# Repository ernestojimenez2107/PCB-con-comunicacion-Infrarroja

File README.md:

<h1 align="center">📡 PCB de 4 capas · Arduino Nano + Infrarrojos</h1><p align="center">
  Del esquema eléctrico a una placa preparada para su revisión y fabricación.
  <br>
  <strong>Proyecto académico · EITE · Universidad de Las Palmas de Gran Canaria</strong>
</p>✨ ¿De qué trata el proyecto?
Diseño de una placa de circuito impreso (PCB) de cuatro capas con Arduino Nano, conectores de expansión y un sistema de transmisión y recepción por infrarrojos. El circuito integra un oscilador de aproximadamente 40 kHz basado en un temporizador SE555D, lógica digital para controlar las señales y una etapa emisora y receptora de infrarrojos.

🔁 Diagrama de bloques

```mermaid
flowchart LR
    A["Arduino Nano"] -->|TX y control| L["Lógica digital"]
    O["Oscilador SE555D · 40 kHz"] --> L
    L --> E["LED IR · TSAL4400"]
    R["Receptor IR · TSOP18440"] --> X["Lógica de recepción"]
    X -->|RX| A
```
 Componentes principales
Bloque	Componentes / función

🧠 Control	Arduino Nano y conectores de expansión

⏱️ Oscilador	SE555D, señal de ~40 kHz

📤 Emisor IR	LED TSAL4400 y transistor MMBT2222A

📥 Receptor IR	TSOP18440

🔀 Lógica digital	74LVC2G86 y 74LVC2G08

⚡ Alimentación	Redes de 5 V, 3,3 V y masa

 Diseño de la PCB

Capa	Uso principal

🔴 TOP	Pistas y conexiones de la cara superior

🟢 GND	Plano interno de masa

🟠 POWER	Distribución de alimentación

🔵 BOTTOM	Pistas y conexiones de la cara inferior

La PCB incluye conectores, taladros de fijación, serigrafía y planos de cobre.
✅ Comprobaciones realizadas
- DRC de KiCad: 0 errores y 0 avisos en la última comprobación indicada.
- Archivos de fabricación: Gerber de las cuatro capas, máscaras, serigrafías y contorno.
- Taladrado: archivos PTH y NPTH generados.
- Montaje: archivo CSV de posición de componentes generado.
- Documentación: esquemas y capas de la PCB exportados a PDF.
[!IMPORTANT]
Antes de fabricar la PCB, hay que revisar los Gerber en el visor del fabricante y confirmar la compatibilidad de las huellas, la colocación de los conectores y los modelos 3D.

📂 Organización del repositorio

Practica_Diseno_PCB/
├── Práctica_Diseño_PCB.kicad_pro    # Proyecto KiCad

├── Práctica_Diseño_PCB.kicad_sch    # Esquema principal

├── Práctica_Diseño_PCB.kicad_pcb    # Diseño de la placa

├── arduino.kicad_sch               # Arduino y expansión

├── oscilador.kicad_sch             # Oscilador de 40 kHz

├── IR_Tx_Rx.kicad_sch              # Transmisor y receptor IR

├── alimentaciones.kicad_sch       # Alimentaciones

├── Fabricacion_PCB/                # Gerber y taladrado

├── Archivos de Montaje_PCB/        # Posiciones de componentes

├── Documentacion_PDF/              # PDF del esquema y la placa

La estructura muestra los archivos principales; los nombres de las carpetas de documentación pueden variar según la entrega.

El archivo de posición de componentes se encuentra en la carpeta de montaje. La BOM y el presupuesto de 10 y 100 placas forman parte de la documentación del proyecto, cuando se incluyan en el repositorio.
🎓 Contexto académico
Proyecto desarrollado para una práctica de diseño de circuitos impresos de la Escuela de Ingeniería de Telecomunicación y Electrónica (EITE) de la Universidad de Las Palmas de Gran Canaria (ULPGC).
<p align="center"><strong>🛠️ Diseñado con KiCad </strong></p>

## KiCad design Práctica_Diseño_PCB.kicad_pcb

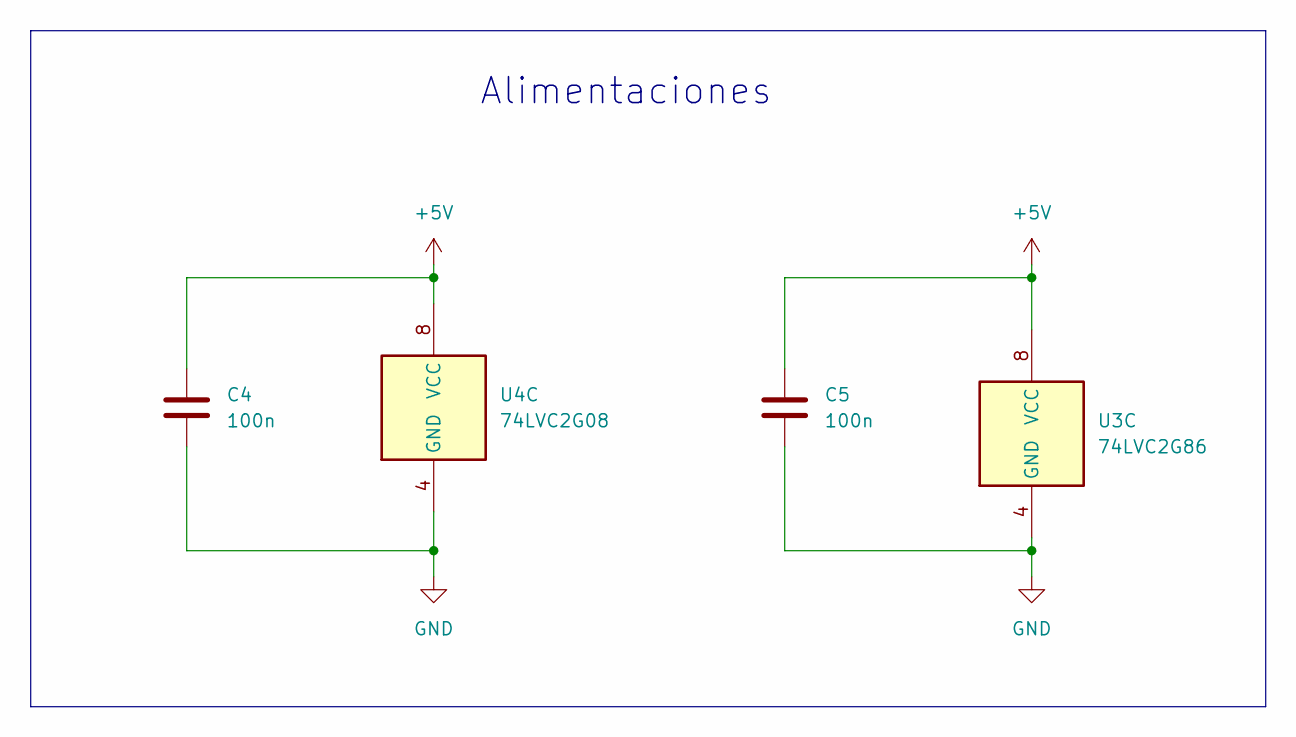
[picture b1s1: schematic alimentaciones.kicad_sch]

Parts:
C4, C5: 100n; C_0805_2012Metric_Pad1.18x1.45mm_HandSolder; DigiKey 1276-2442-1-ND
U3: 74LVC2G86; VSSOP-8_3x3mm_P0.65mm; DigiKey 296-13275-1-ND
U4: 74LVC2G08; VSSOP-8_3x3mm_P0.65mm; DigiKey 296-13263-1-ND

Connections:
+5V: C4.1, C5.1, U3.8 (VCC), U4.8 (VCC); also elsewhere on the board
GND: C4.2, C5.2, U3.4 (GND), U4.4 (GND); also elsewhere on the board

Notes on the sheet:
Alimentaciones

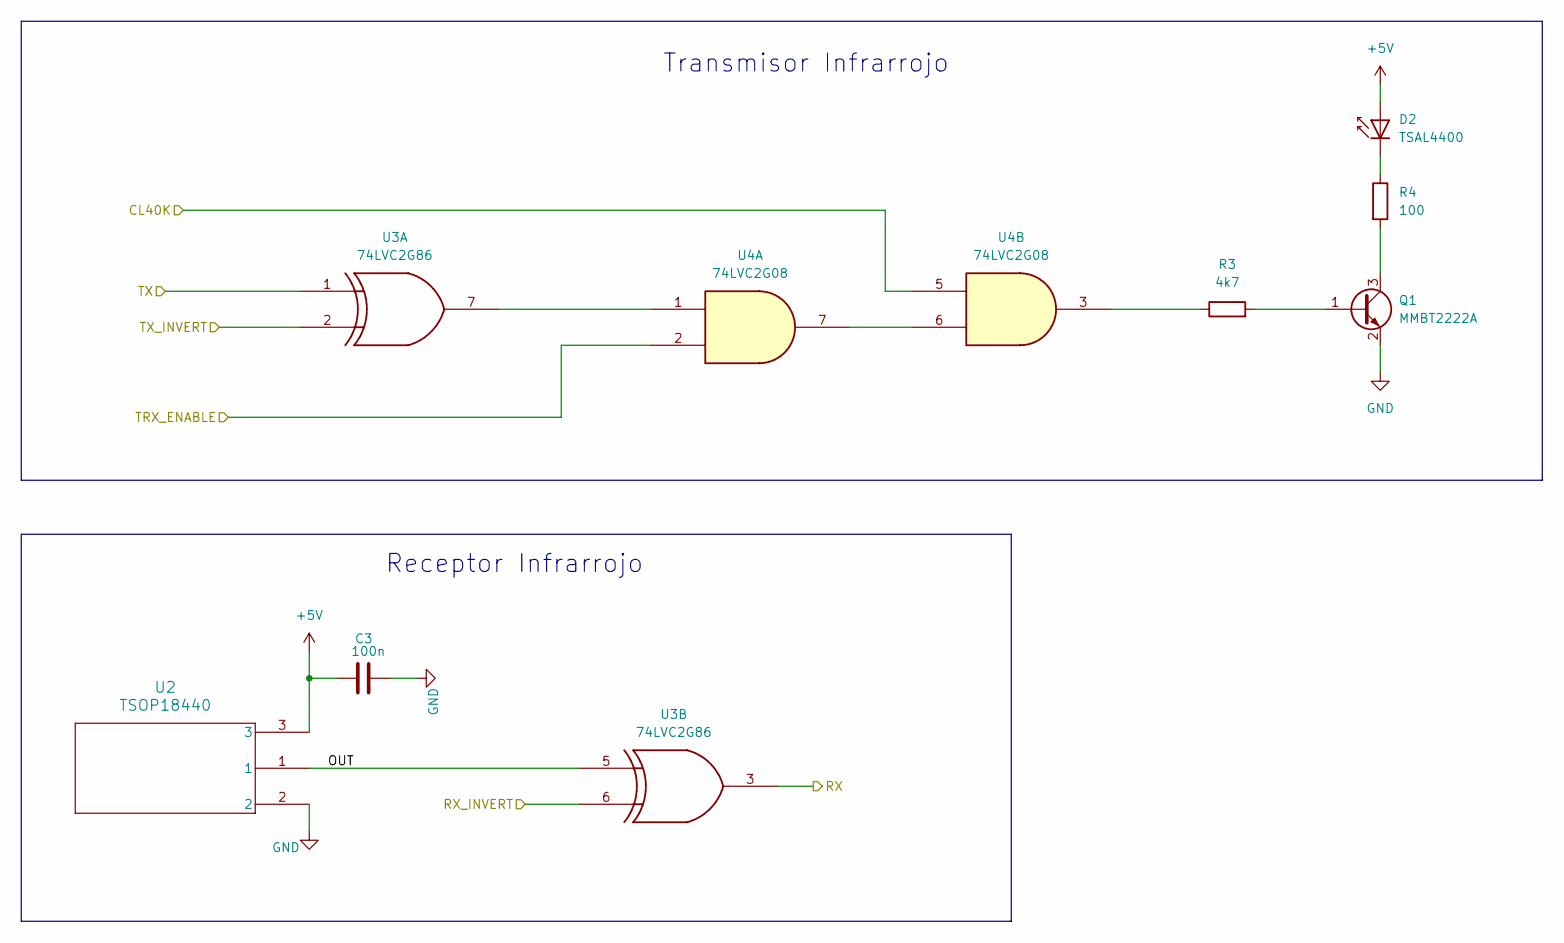
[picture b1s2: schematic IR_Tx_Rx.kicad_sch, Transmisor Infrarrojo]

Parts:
C3: 100n; C_0805_2012Metric_Pad1.18x1.45mm_HandSolder; DigiKey 1276-2442-1-ND
D2: TSAL4400; LED_D3.0mm_IRBlack; DigiKey 751-1201-ND
Q1: MMBT2222A; SOT-23; DigiKey MMBT2222ATPMSCT-ND
R3: 4k7; R_0805_2012Metric_Pad1.20x1.40mm_HandSolder; DigiKey RMCF0805JT4K70CT-ND
R4: 100; R_0805_2012Metric_Pad1.20x1.40mm_HandSolder; DigiKey RMCF0805JT100RCT-ND
U2: TSOP18440; Vishay_MOLD-3Pin; DigiKey TSOP18440-ND
U3: 74LVC2G86; VSSOP-8_3x3mm_P0.65mm; DigiKey 296-13275-1-ND
U4: 74LVC2G08; VSSOP-8_3x3mm_P0.65mm; DigiKey 296-13263-1-ND

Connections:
+5V: C3.2, D2.2 (A), U2.3; also elsewhere on the board
/Arduino Nano/RX: U3.3; also elsewhere on the board
/Arduino Nano/RX_INVERT: U3.6; also elsewhere on the board
/Arduino Nano/TRX_ENABLE: U4.2; also elsewhere on the board
/Arduino Nano/TX: U3.1; also elsewhere on the board
/Arduino Nano/TX_INVERT: U3.2; also elsewhere on the board
/Oscilador/CL40K: U4.5; also elsewhere on the board
/Tx_Rx_Infrarrojo/OUT: U2.1, U3.5
GND: C3.1, Q1.2 (E), U2.2; also elsewhere on the board
unnamed: D2.1 (K), R4.1
unnamed: Q1.1 (B), R3.2
unnamed: Q1.3 (C), R4.2
unnamed: R3.1, U4.3
unnamed: U3.7, U4.1
unnamed: U4.6, U4.7

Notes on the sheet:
Transmisor Infrarrojo
Receptor Infrarrojo

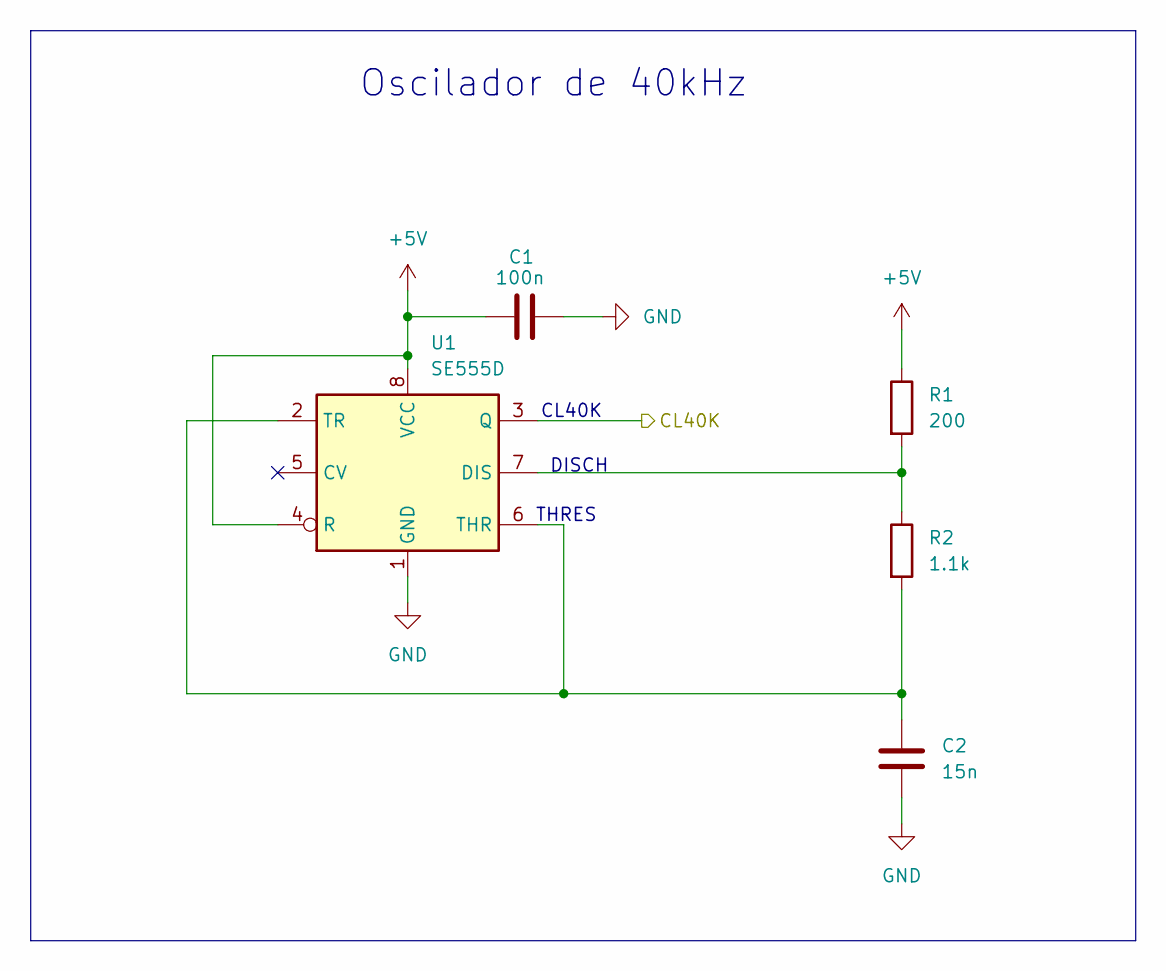
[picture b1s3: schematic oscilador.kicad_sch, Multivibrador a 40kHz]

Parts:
C1: 100n; C_0805_2012Metric_Pad1.18x1.45mm_HandSolder; DigiKey 1276-2442-1-ND
C2: 15n; C_0805_2012Metric_Pad1.18x1.45mm_HandSolder; DigiKey 311-4273-1-ND
R1: 200; R_0805_2012Metric_Pad1.20x1.40mm_HandSolder; DigiKey RMCF0805JT200RCT-ND
R2: 1.1k; R_0805_2012Metric_Pad1.20x1.40mm_HandSolder; DigiKey RMCF0805JT1K10CT-ND
U1: SE555D; SOIC-8_3.9x4.9mm_P1.27mm; DigiKey 296-6501-1-ND

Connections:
+5V: C1.1, R1.1, U1.4 (R), U1.8 (VCC); also elsewhere on the board
/Oscilador/CL40K: U1.3 (Q); also elsewhere on the board
GND: C1.2, C2.2, U1.1 (GND); also elsewhere on the board
unnamed: R1.2, R2.1, U1.7 (DIS)
unnamed: C2.1, R2.2, U1.2 (TR), U1.6 (THR)

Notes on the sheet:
THRES
DISCH
CL40K
Oscilador de 40kHz

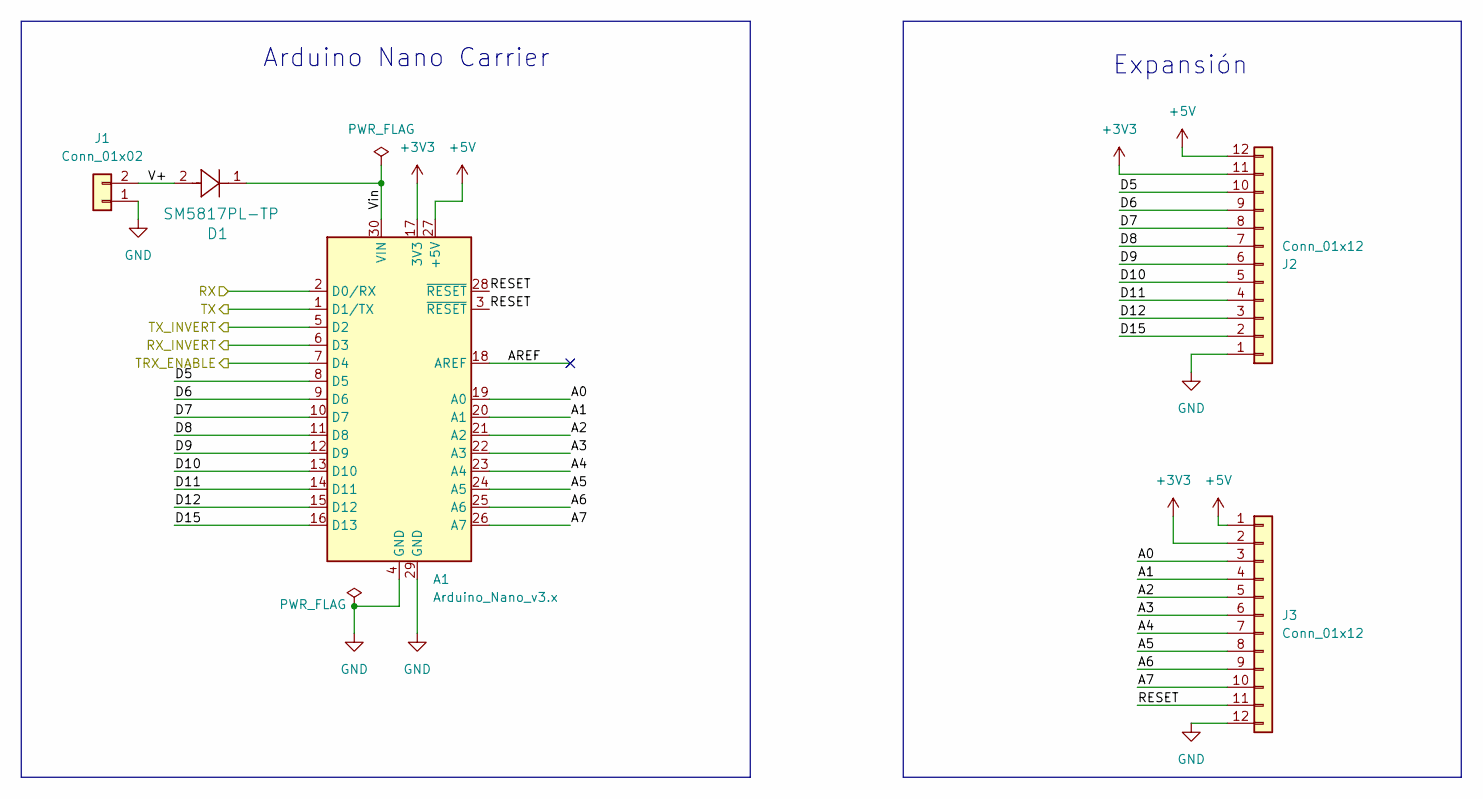
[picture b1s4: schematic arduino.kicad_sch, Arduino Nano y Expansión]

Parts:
A1: Arduino_Nano_v3.x; Arduino_Nano; DigiKey 1050-1001-ND
D1: SM5817PL-TP; CR_5817PL-TP_MCC; DigiKey SM5817PL-TPMSCT-ND
J1: Conn_01x02; 282837-2_TYC; DigiKey A113320-ND
J2, J3: Conn_01x12; PinHeader_1x12_P2.54mm_Vertical; DigiKey 2057-PH1-12-UA-ND

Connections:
+3V3: A1.17 (3V3), J2.11, J3.2
+5V: A1.27 (+5V), J2.12, J3.1; also elsewhere on the board
/Arduino Nano/A0: A1.19 (A0), J3.3
/Arduino Nano/A1: A1.20 (A1), J3.4
/Arduino Nano/A2: A1.21 (A2), J3.5
/Arduino Nano/A3: A1.22 (A3), J3.6
/Arduino Nano/A4: A1.23 (A4), J3.7
/Arduino Nano/A5: A1.24 (A5), J3.8
/Arduino Nano/A6: A1.25 (A6), J3.9
/Arduino Nano/A7: A1.26 (A7), J3.10
/Arduino Nano/AREF: A1.18 (AREF)
/Arduino Nano/D5: A1.8 (D5), J2.10
/Arduino Nano/D6: A1.9 (D6), J2.9
/Arduino Nano/D7: A1.10 (D7), J2.8
/Arduino Nano/D8: A1.11 (D8), J2.7
/Arduino Nano/D9: A1.12 (D9), J2.6
/Arduino Nano/D10: A1.13 (D10), J2.5
/Arduino Nano/D11: A1.14 (D11), J2.4
/Arduino Nano/D12: A1.15 (D12), J2.3
/Arduino Nano/D15: A1.16 (D13), J2.2
/Arduino Nano/RESET: A1.3 (~RESET), A1.28 (~RESET), J3.11
/Arduino Nano/RX: A1.2 (D0/RX); also elsewhere on the board
/Arduino Nano/RX_INVERT: A1.6 (D3); also elsewhere on the board
/Arduino Nano/TRX_ENABLE: A1.7 (D4); also elsewhere on the board
/Arduino Nano/TX: A1.1 (D1/TX); also elsewhere on the board
/Arduino Nano/TX_INVERT: A1.5 (D2); also elsewhere on the board
/Arduino Nano/V+: D1.2, J1.2
/Arduino Nano/Vin: A1.30 (VIN), D1.1
GND: A1.4 (GND), A1.29 (GND), J1.1, J2.1, J3.12; also elsewhere on the board

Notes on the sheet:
Arduino Nano Carrier
Expansión

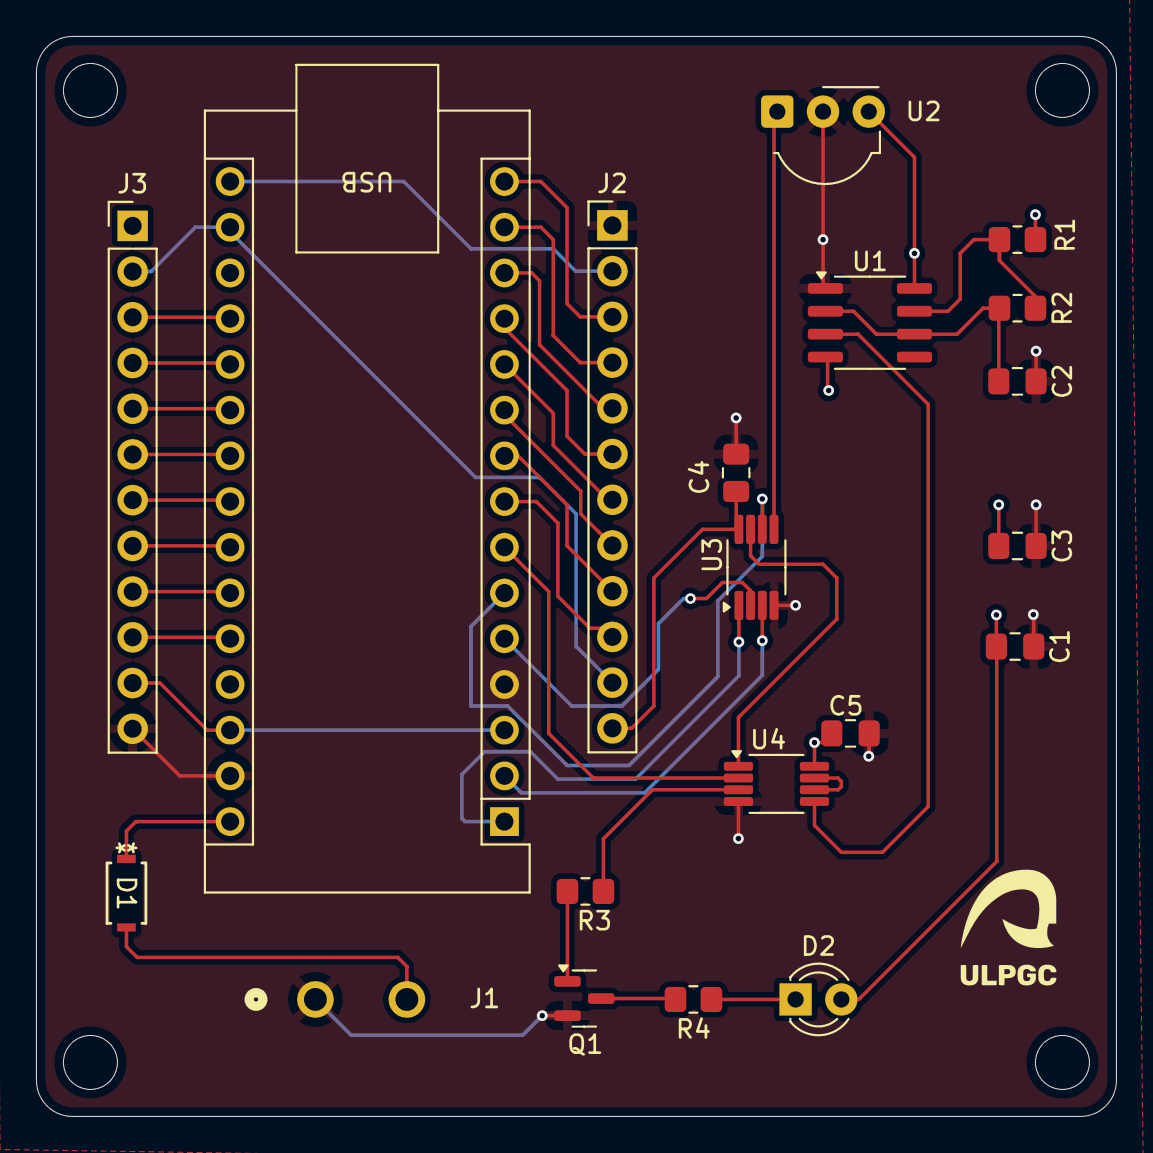
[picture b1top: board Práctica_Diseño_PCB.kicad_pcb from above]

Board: 4 copper layers, 60.0 x 60.0 mm, 20 parts (1 on the bottom side), 38 nets.

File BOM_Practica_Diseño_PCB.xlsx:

Reference | Qty | Value | Footprint | Datasheet | Fabricante | Modelo | Proveedor | DigiKey | Descripción
A1 | 1 | Arduino_Nano_v3.x | MisPlacas:Arduino_Nano | https://mm.digikey.com/Volume0/opasdata/d220001/medias/docus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 | Arduino | A000005 | DigiKey | 1050-1001-ND | Arduino Nano v3.x
C1,C3,C4,C5 | 4 | 100n | Capacitor_SMD:C_0805_2012Metric_Pad1.18x1.45mm_HandSolder | https://mm.digikey.com/Volume0/opasdata/d220001/medias/docus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 | Samsung Electro-Mechanics | CL21B104KACNFNC | DigiKey | 1276-2442-1-ND | 0.1 µF ±10% 25V Ceramic Capacitor X7R 0805 (2012 Metric)
C2 | 1 | 15n | Capacitor_SMD:C_0805_2012Metric_Pad1.18x1.45mm_HandSolder | https://yageogroup.com/content/datasheet/asset/file/UPY-GPHC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 | YAGEO | CC0805JRX7R9BB153 | DigiKey | 311-4273-1-ND | Unpolarized capacitor
D1 | 1 | SM5817PL-TP | MisDiodos:CR_5817PL-TP_MCC | https://www.mccsemi.com/pdf/Products/SM5817PL-SM5819PL(SOD-1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 | MCC (Micro Commercial Components) | SM5817PL-TP | DigiKey | SM5817PL-TPMSCT-ND | Diodo 20 V 1A Montaje superficial SOD-123FL
D2 | 1 | TSAL4400 | LED_THT:LED_D3.0mm_IRBlack | http://www.vishay.com/docs/81006/tsal4400.pdf | Vishay Semiconductor Opto Division | TSAL4400 | DigiKey | 751-1201-ND | Infrared (IR) Emitter 940nm 1.35V 100mA 16mW/sr @ 100mA 50° Radial, 3mm Dia (T-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
J1 | 1 | Conn_01x02 | MisTerminales:282837-2_TYC | https://www.te.com/commerce/DocumentDelivery/DDEController?A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 | TE Connectivity AMP Connectors | 282837-2 | DigiKey | A113320-ND | Generic connector, single row, 01x02, script generated (kicad-library-utils/sch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
J2,J3 | 2 | Conn_01x12 | Connector_PinHeader_2.54mm:PinHeader_1x12_P2.54mm_Vertical | https://app.adam-tech.com/products/download/data_sheet/20160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 | Adam Tech | PH1-12-UA | DigiKey | 2057-PH1-12-UA-ND | Generic connector, single row, 01x12, script generated (kicad-library-utils/sch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
Q1 | 1 | MMBT2222A | Package_TO_SOT_SMD:SOT-23 | https://www.mccsemi.com/pdf/Products/MMBT2222A(SOT-23).pdf | MCC (Micro Commercial Components) | MMBT2222A-TP | DigiKey | MMBT2222ATPMSCT-ND | Bipolar (BJT) Transistor NPN 40 V 600 mA 300MHz 350 mW Surface Mount SOT-23
R1 | 1 | 200 | Resistor_SMD:R_0805_2012Metric_Pad1.20x1.40mm_HandSolder | https://www.seielect.com/catalog/SEI-RMCF_RMCP.pdf | Stackpole Electronics Inc | RMCF0805JT200R | DigiKey | RMCF0805JT200RCT-ND | Resistor
R2 | 1 | 1.1k | Resistor_SMD:R_0805_2012Metric_Pad1.20x1.40mm_HandSolder | https://www.seielect.com/catalog/SEI-RMCF_RMCP.pdf | Stackpole Electronics Inc | RMCF0805JT1K10 | DigiKey | RMCF0805JT1K10CT-ND | 1.1 kOhms ±5% 0.125W, 1/8W Chip Resistor 0805 (2012 Metric) Automotive AEC-Q200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
R3 | 1 | 4k7 | Resistor_SMD:R_0805_2012Metric_Pad1.20x1.40mm_HandSolder | https://www.seielect.com/catalog/SEI-RMCF_RMCP.pdf | Stackpole Electronics Inc | RMCF0805JT4K70 | DigiKey | RMCF0805JT4K70CT-ND | 4.7 kOhms ±5% 0.125W, 1/8W Resistencia en microprocesador 0805 (2012 métrico) A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
R4 | 1 | 100 | Resistor_SMD:R_0805_2012Metric_Pad1.20x1.40mm_HandSolder | https://www.seielect.com/catalog/SEI-RMCF_RMCP.pdf | Stackpole Electronics Inc | RMCF0805JT100R | DigiKey | RMCF0805JT100RCT-ND | 100 Ohms ±5% 0.125W, 1/8W Chip Resistor 0805 (2012 Metric) Automotive AEC-Q200 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
U1 | 1 | SE555D | Package_SO:SOIC-8_3.9x4.9mm_P1.27mm | http://www.ti.com/lit/ds/symlink/ne555.pdf | Texas Instruments | NE555DR | DigiKey | 296-6501-1-ND | Precision Timers, 555 compatible, SOIC-8
U2 | 1 | TSOP18440 | OptoDevice:Vishay_MOLD-3Pin | https://www.vishay.com/docs/82739/tsop184.pdf | Vishay Semiconductor Opto Division | TSOP18440 | DigiKey | TSOP18440-ND | Remote Receiver Sensor 40.0kHz 24m Through Hole
U3 | 1 | 74LVC2G86 | Package_SO:VSSOP-8_3x3mm_P0.65mm | https://www.ti.com/lit/ds/symlink/sn74lvc2g08.pdf?HQS=dis-dk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 | Texas Instruments | SN74LVC2G86DCUR | DigiKey | 296-13275-1-ND | XOR (OR exclusivo) IC 2 Canal 8-VSSOP
U4 | 1 | 74LVC2G08 | Package_SO:VSSOP-8_3x3mm_P0.65mm | http://www.ti.com/lit/sg/scyt129e/scyt129e.pdf | Texas Instruments | SN74LVC2G08DCTR | DigiKey | 296-13263-1-ND | Dual AND Gate, Low-Voltage CMOS
